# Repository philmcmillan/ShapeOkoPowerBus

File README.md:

ShapeOkoPowerBus
================

EAGLE project for laying out a small power distribution bus for a ShapeOko CNC mill.

I'm at the noob/beginner stage in electronics and PCB design. I am sick of wires everywhere with the CNC mill I built and decided to build a power distribution bus on a board to minimize all the wires running between the components I plan to put in an enclosure. Use at your own risk - I make no representations that I am doing this correctly - in fact I have problably screwed something up.

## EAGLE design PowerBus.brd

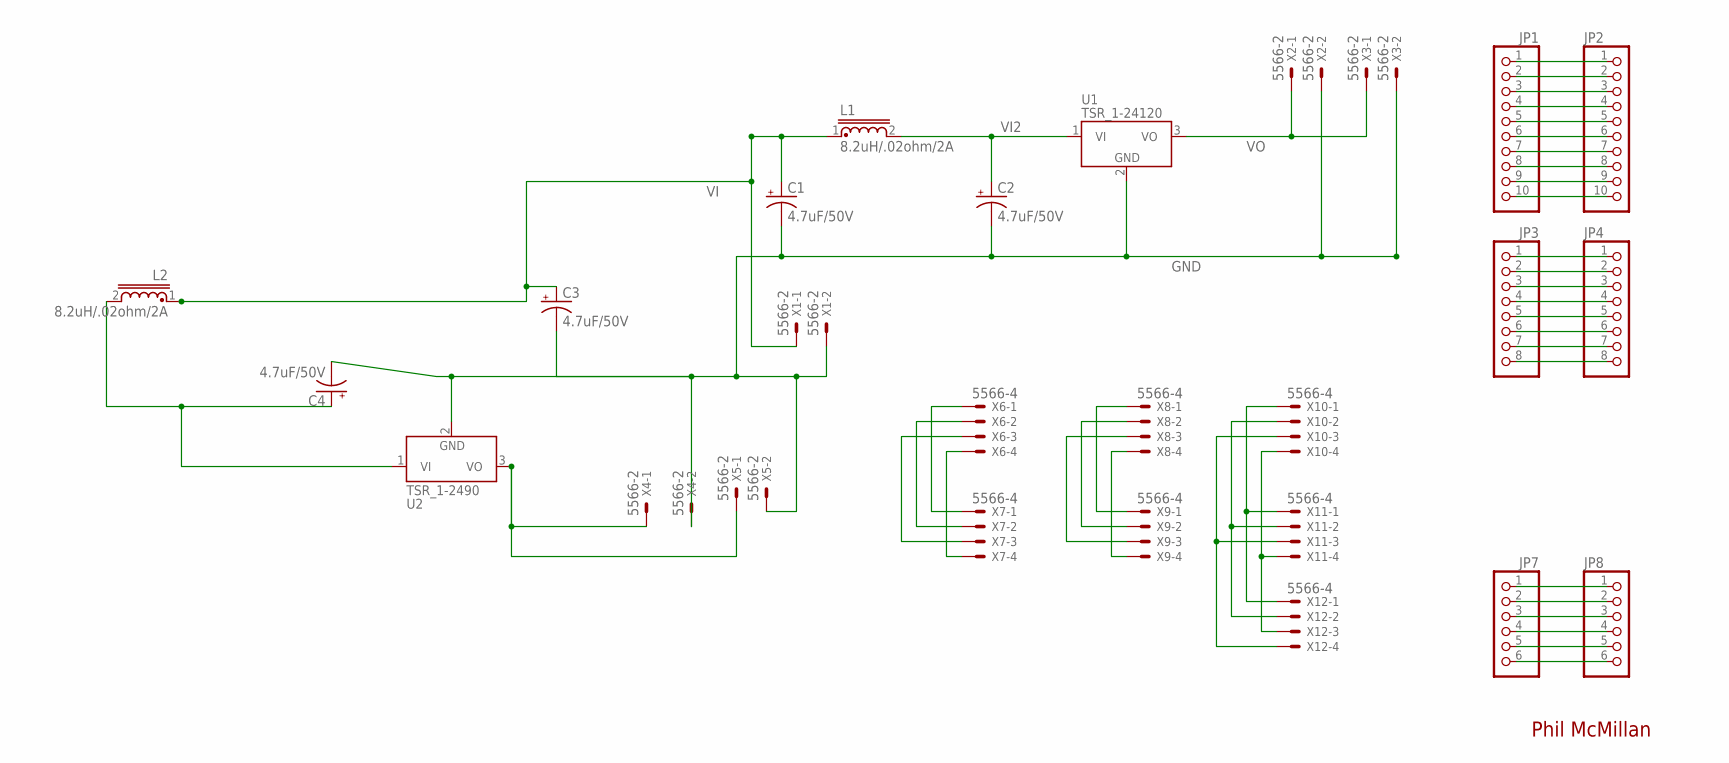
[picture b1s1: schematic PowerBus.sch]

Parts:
C1, C2, C3, C4: 4.7uF/50V; E2-5
JP1, JP2: PINHD-1X10; 1X10
JP3, JP4: PINHD-1X8; 1X08
JP7, JP8: PINHD-1X6; 1X06
L1, L2: 8.2uH/.02ohm/2A; MCAP103722016A-8R2MU
U1: TSR_1-24120; TSR-1
U2: TSR_1-2490; TSR-1
X1, X2, X3, X4, X5: 5566-2
X6, X7, X8, X9, X10, X11, X12: 5566-4

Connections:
GND: C1.-, C2.-, C3.-, C4.-, U1.2 (GND), U2.2 (GND), X1.2, X2.2, X3.2, X4.2, X5.2
unnamed: X6.1, X7.1
unnamed: X6.2, X7.2
unnamed: X6.3, X7.3
unnamed: X6.4, X7.4
unnamed: JP1.1, JP2.1
unnamed: JP1.2, JP2.2
unnamed: X8.1, X9.1
unnamed: X8.2, X9.2
unnamed: X8.3, X9.3
unnamed: X8.4, X9.4
unnamed: X10.1, X11.1, X12.1
unnamed: X10.2, X11.2, X12.2
unnamed: X10.3, X11.3, X12.4
unnamed: X10.4, X11.4, X12.3
unnamed: JP1.3, JP2.3
unnamed: JP1.5, JP2.5
unnamed: JP1.6, JP2.6
unnamed: JP1.7, JP2.7
unnamed: JP1.8, JP2.8
unnamed: JP1.9, JP2.9
unnamed: JP1.10, JP2.10
unnamed: JP1.4, JP2.4
unnamed: JP3.1, JP4.1
unnamed: JP3.2, JP4.2
unnamed: JP3.3, JP4.3
unnamed: JP3.4, JP4.4
unnamed: JP3.5, JP4.5
unnamed: JP3.6, JP4.6
unnamed: JP3.7, JP4.7
unnamed: JP3.8, JP4.8
unnamed: JP7.1, JP8.1
unnamed: JP7.2, JP8.2
unnamed: JP7.3, JP8.3
unnamed: JP7.4, JP8.4
unnamed: JP7.5, JP8.5
unnamed: JP7.6, JP8.6
VI: C1.+, C3.+, L1.1, L2.1, X1.1
VI2: C2.+, L1.2, U1.1 (VI)
VI3: C4.+, L2.2, U2.1 (VI)
VO: U1.3 (VO), X2.1, X3.1
VO2: U2.3 (VO), X4.1, X5.1

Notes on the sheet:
Phil McMillan

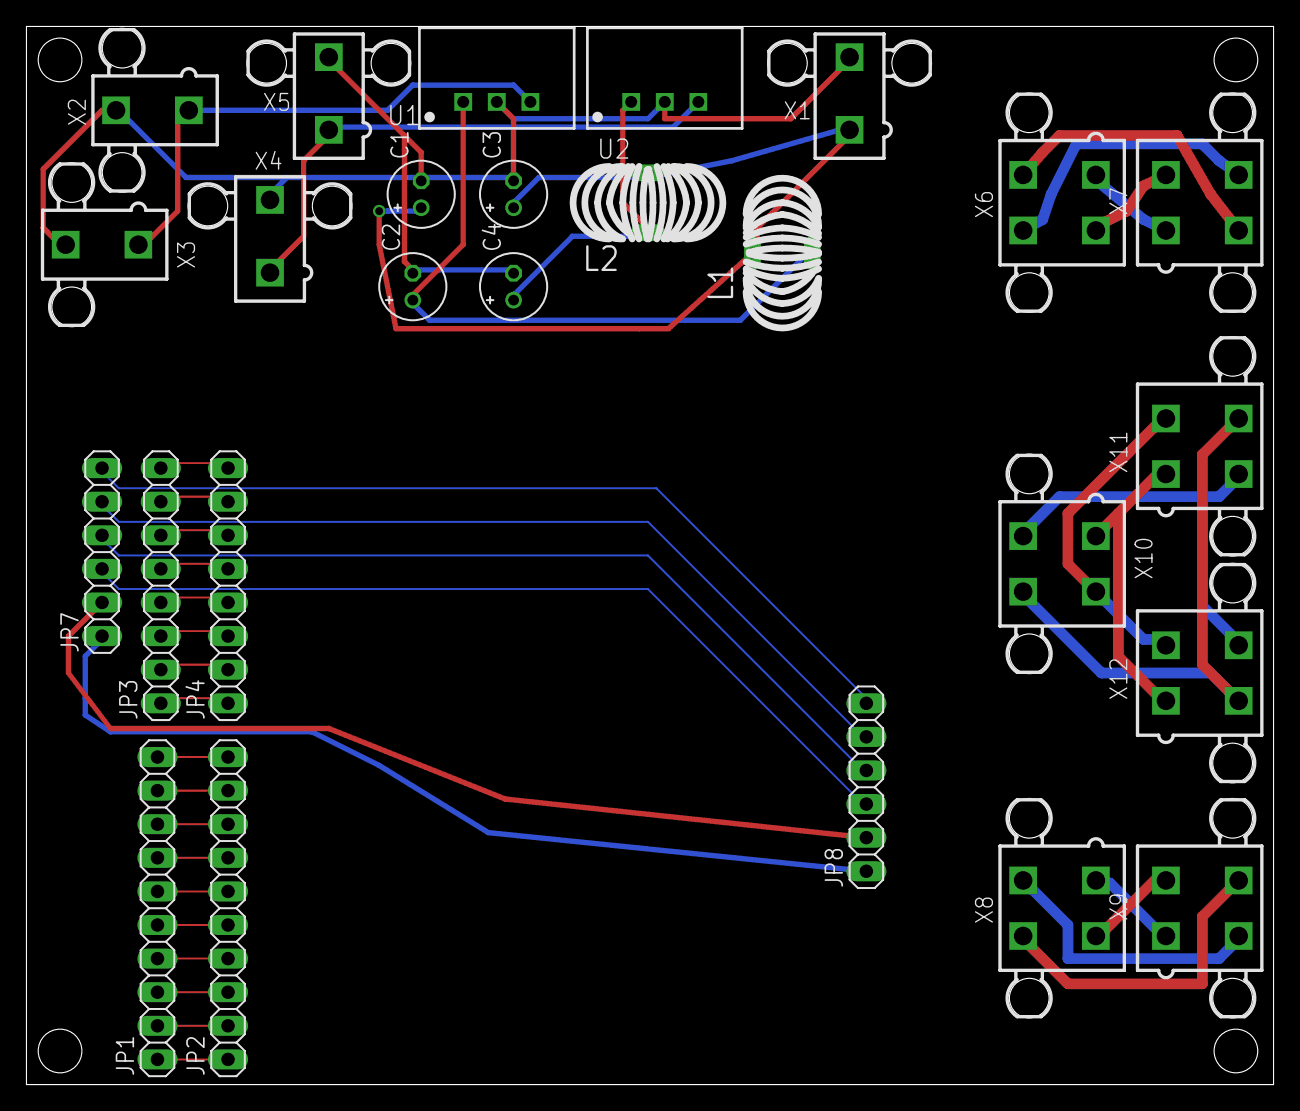
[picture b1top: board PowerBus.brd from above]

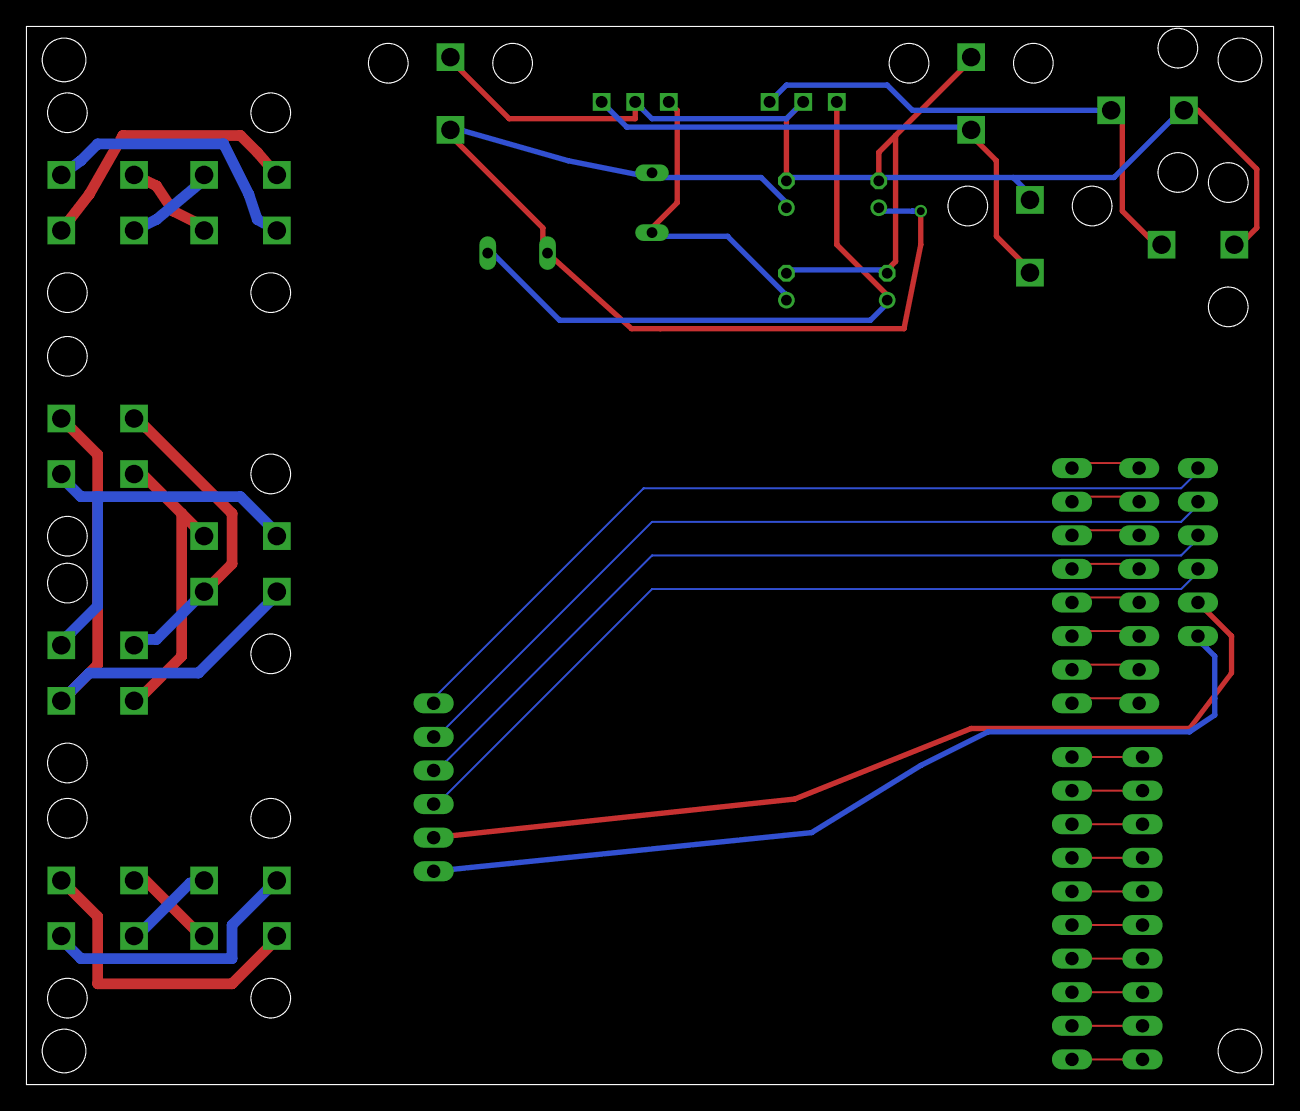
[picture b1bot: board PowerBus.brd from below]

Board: 2 copper layers, 94.3 x 80.0 mm, 30 parts (2 on the bottom side), 42 nets.

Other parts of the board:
U$1, U$2, U$4, U$5: STAND-OFF

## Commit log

2013-05-27 PM - Updated read me with dire warnings of my competence
2013-05-27 PM - Initiated project. Started schematic.
2013-06-03 PM - Updated schematic; created board layout
2013-12-09 PM - Updated schematic and board. Initial prototype from OSHPark

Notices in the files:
parts and their libraries:
SparkFun-Electromechanical: Licensing: CC v3.0 Share-Alike You are welcome to use this library for commercial purposes.
